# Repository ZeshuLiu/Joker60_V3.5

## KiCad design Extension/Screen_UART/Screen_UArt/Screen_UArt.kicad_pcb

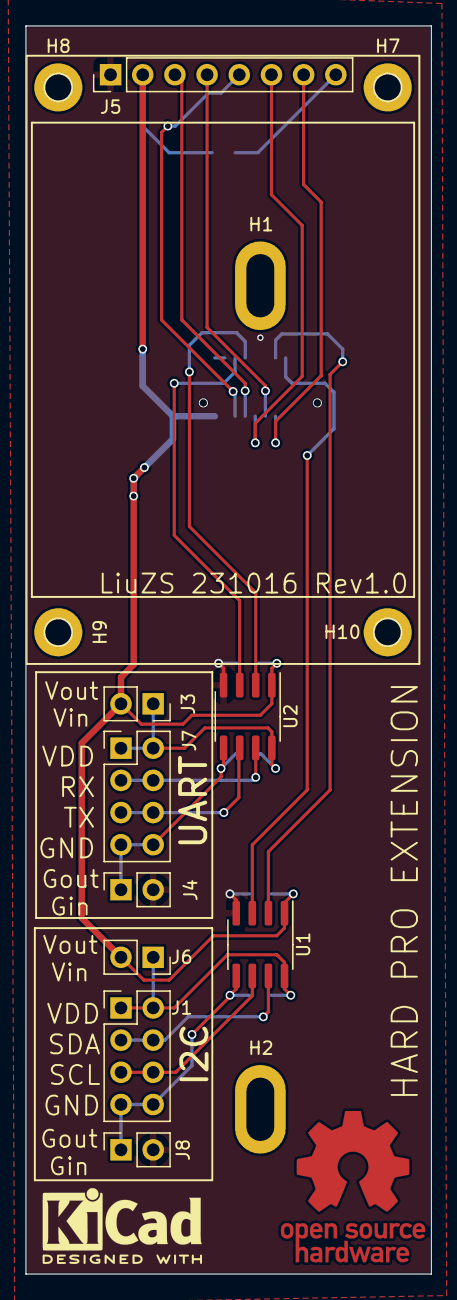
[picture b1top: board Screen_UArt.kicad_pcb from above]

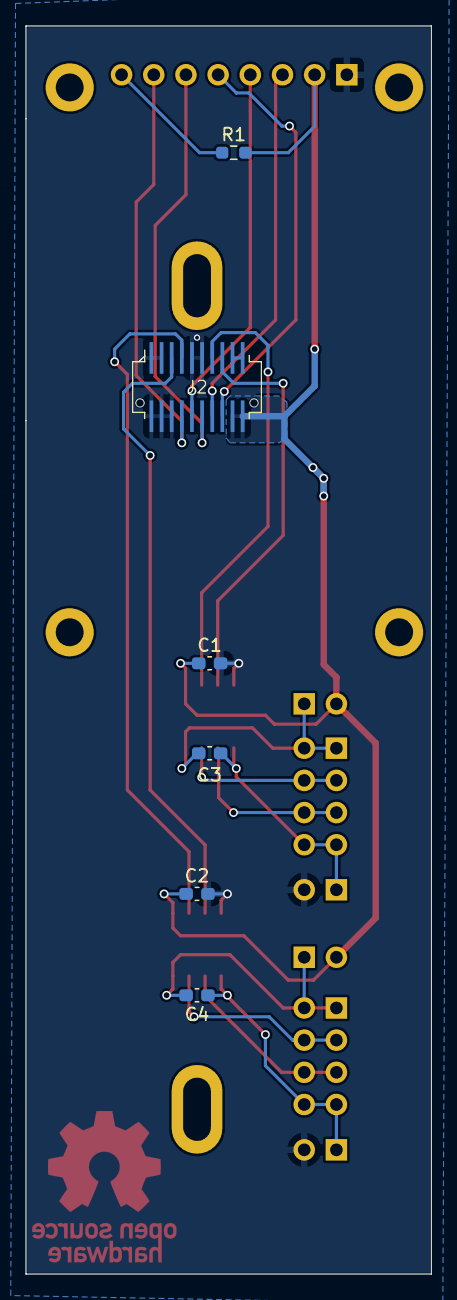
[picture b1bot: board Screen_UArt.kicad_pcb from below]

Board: 2 copper layers, 32.0 x 98.5 mm, 21 parts (6 on the bottom side), 21 nets.

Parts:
C1, C2, C3, C4: 100nf; C_0603_1608Metric_Pad1.08x0.95mm_HandSolder
H1, H2: MountingHole_Pad; MountingHole_M2_2.2x5mm_pad
H7, H8, H9, H10: MountingHole_Pad; MountingHole_2.2mm_M2_DIN965_Pad
J1, J7: Conn_02x04_Odd_Even; PinHeader_2x04_P2.54mm_Vertical
J2: Conn_02x10_Counter_Clockwise; BTB_0.8mm_2x10pin_Male
J3, J4, J6, J8: Conn_01x02_Pin; PinSocket_1x02_P2.54mm_Vertical
J5: Conn_01x08_Pin; PinHeader_1x08_P2.54mm_Vertical
R1: 10k; R_0603_1608Metric_Pad0.98x0.95mm_HandSolder
U1: ADuM1250; SOIC-8_3.9x4.9mm_P1.27mm
U2: ADuM1201BR; SOIC-8_3.9x4.9mm_P1.27mm

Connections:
+5V: J2.1, J2.2
/BLK: J5.8, R1.1
/MISO2: J2.16, J5.6
/MOSI2: J2.15, J5.4
/PB12: J2.18, J5.5
/PC8: J2.14, J5.7
/RXO: J7.3, J7.4, U2.7 (VIA)
/Rx6: J2.4, U2.2 (VOA)
/SCK2: J2.17, J5.3
/SCL3: J2.8, U1.3 (SCL1)
/SCLO: J1.5, J1.6, U1.6 (SCL2)
/SDA3: J2.7, U1.2 (SDA1)
/SDAO: J1.3, J1.4, U1.7 (SDA2)
/TXO: J7.5, J7.6, U2.6 (VOB)
/Tx6: J2.3, U2.3 (VIB)
GND: C1.2, C2.2, J2.5, J2.6, J2.9, J2.10, J2.11, J2.12, J2.13, J4.2, J5.1, J8.2, U1.4 (GND1), U2.4 (GND1)
GND1: C4.2, J1.7, J1.8, J8.1, U1.5 (GND2)
GNDA: C3.2, J4.1, J7.7, J7.8, U2.5 (GND2)
VDD: C1.1, C2.1, J2.19, J2.20, J3.2, J5.2, J6.2, R1.2, U1.1 (VDD1), U2.1 (VDD1)
VDDA: C3.1, J3.1, J7.1, J7.2, U2.8 (VDD2)
VDDF: C4.1, J1.1, J1.2, J6.1, U1.8 (VDD2)

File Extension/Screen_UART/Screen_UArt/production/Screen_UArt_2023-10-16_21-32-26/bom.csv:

Designator,Footprint,Quantity,Value,LCSC Part #
"C1, C2, C3, C4",0603,4,100nf,
"H1, H2",MountingHole_M2_2.2x5mm_pad,2,MountingHole_Pad,
"H10, H7, H8, H9",MountingHole_2.2mm_M2_DIN965_Pad,4,MountingHole_Pad,
"J1, J7",PinHeader_2x04_P2.54mm_Vertical,2,Conn_02x04_Odd_Even,
J2,BTB_0.8mm_2x10pin_Male,1,Conn_02x10_Counter_Clockwise,
"J3, J4, J6, J8",PinSocket_1x02_P2.54mm_Vertical,4,Conn_01x02_Pin,
J5,PinHeader_1x08_P2.54mm_Vertical,1,Conn_01x08_Pin,
R1,0603,1,10k,
U1,SOIC-8_3.9x4.9mm_P1.27mm,1,ADuM1250,
U2,SOIC-8_3.9x4.9mm_P1.27mm,1,ADuM1201BR,

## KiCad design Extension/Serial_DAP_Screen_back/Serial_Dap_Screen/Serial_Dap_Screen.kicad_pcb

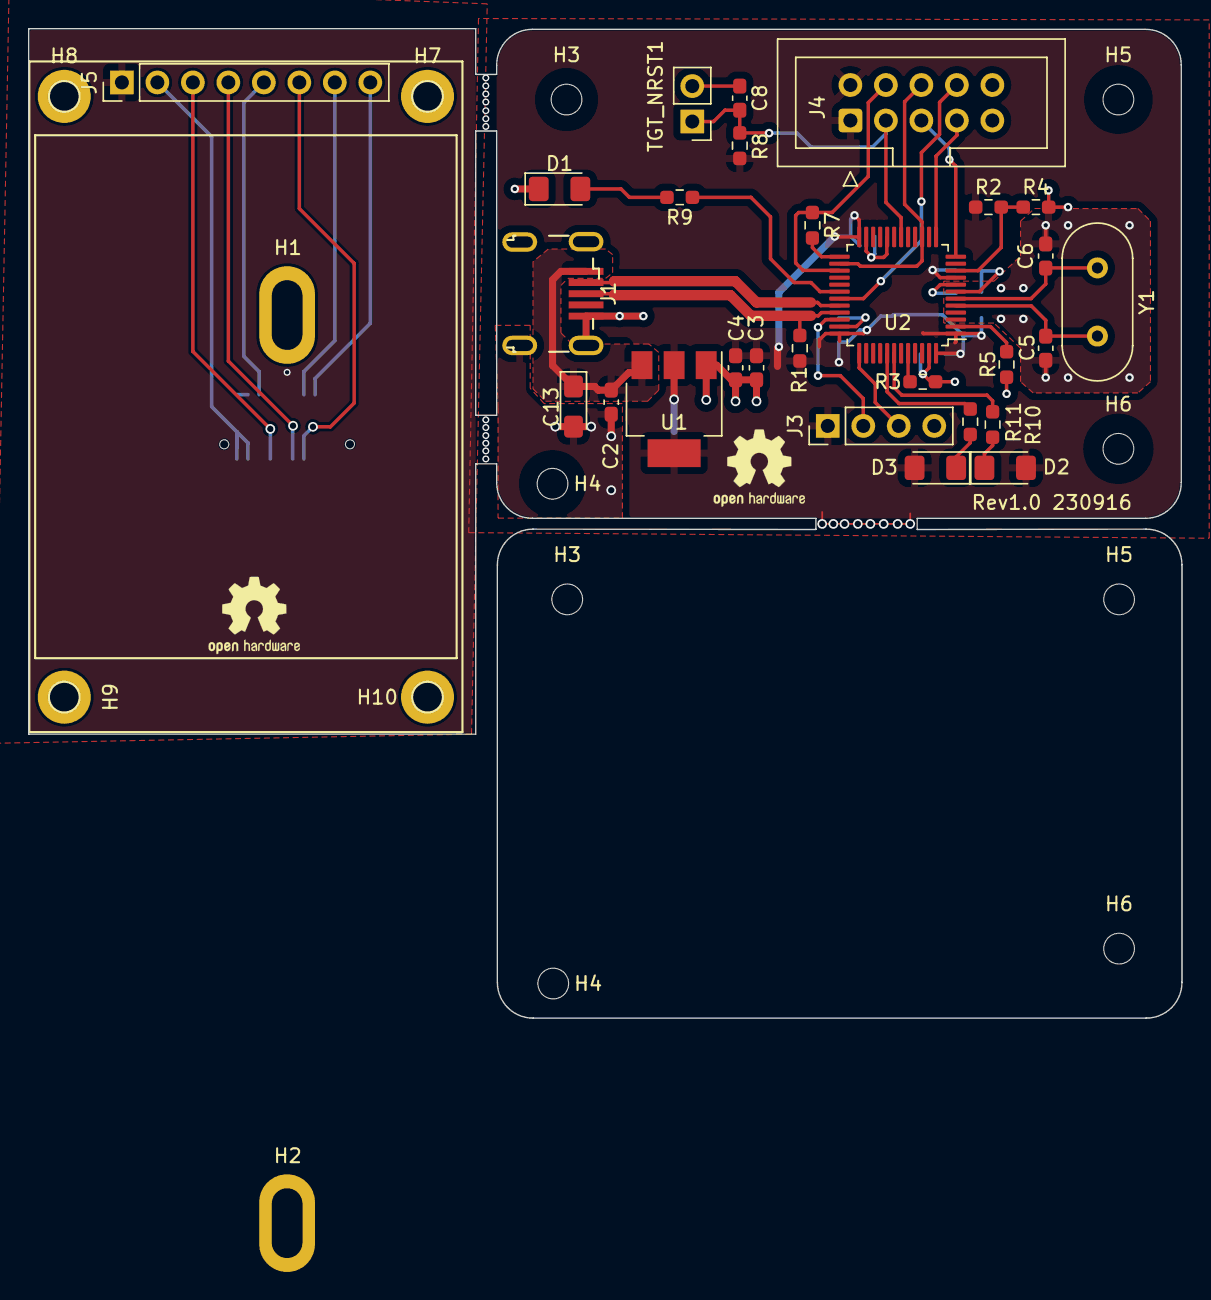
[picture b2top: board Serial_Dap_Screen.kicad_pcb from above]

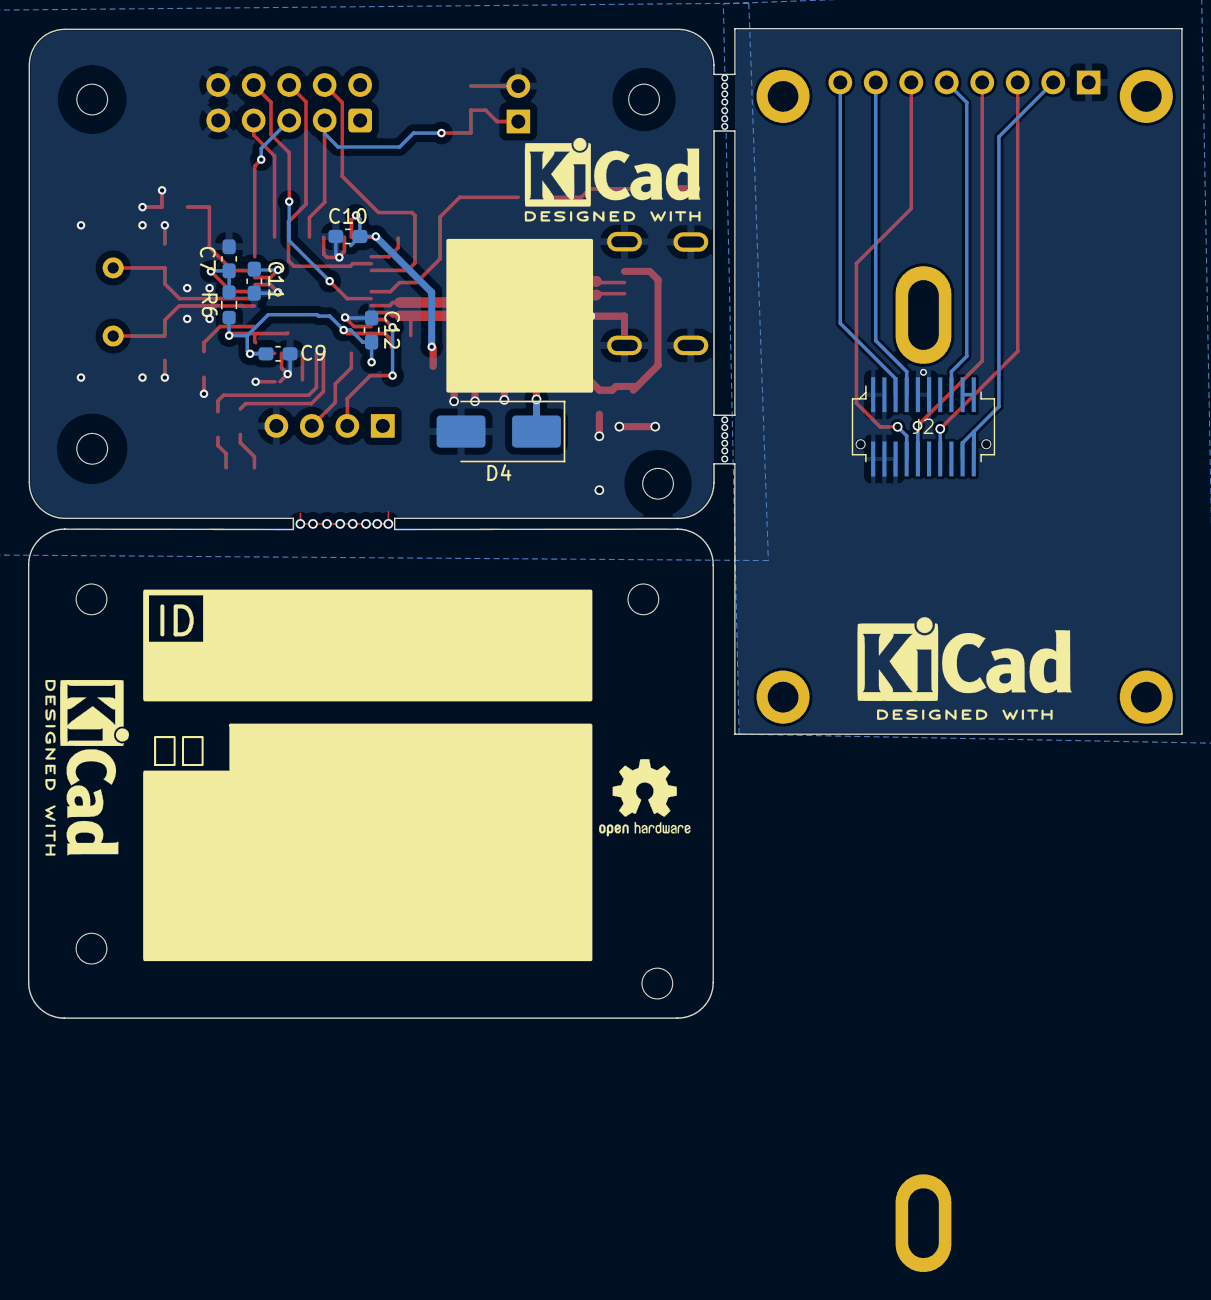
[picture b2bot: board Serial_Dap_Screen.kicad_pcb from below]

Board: 2 copper layers, 82.5 x 70.8 mm, 50 parts (8 on the bottom side), 32 nets.

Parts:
C2, C3, C7, C8, C9, C10, C11, C12: 100nf; C_0603_1608Metric_Pad1.08x0.95mm_HandSolder
C4: 10uf; C_0603_1608Metric_Pad1.08x0.95mm_HandSolder
C5, C6: 20pf; C_0603_1608Metric_Pad1.08x0.95mm_HandSolder
C13: 10uf; CP_EIA-3216-18_Kemet-A_Pad1.58x1.35mm_HandSolder
D1, D2, D3: LED; LED_1206_3216Metric_Pad1.42x1.75mm_HandSolder
D4: SMBJ3.3A; D_SMB_Handsoldering
H1, H2: MountingHole_Pad; MountingHole_M2_2.2x5mm_pad
H3, H3#2, H4, H4#2, H5, H5#2, H6, H6#2: MountingHole; MountingHole_2.2mm_M2
H7, H8, H9, H10: MountingHole_Pad; MountingHole_2.2mm_M2_DIN965_Pad
J1: USB_B_Mini; USB_Micro-B_4TH
J2: Conn_02x10_Counter_Clockwise; BTB_0.8mm_2x10pin_Male
J3: Conn_01x04_Pin; PinHeader_1x04_P2.54mm_Vertical
J4: Conn_02x05_Odd_Even; IDC-Header_2x05_P2.54mm_Vertical
J5: Conn_01x08_Pin; PinHeader_1x08_P2.54mm_Vertical
R1, R10: 1.5k; R_0603_1608Metric_Pad0.98x0.95mm_HandSolder
R2, R4: 4.7k; R_0603_1608Metric_Pad0.98x0.95mm_HandSolder
R3: 100k; R_0603_1608Metric_Pad0.98x0.95mm_HandSolder
R5, R6, R8: 10k; R_0603_1608Metric_Pad0.98x0.95mm_HandSolder
R7: 100; R_0603_1608Metric_Pad0.98x0.95mm_HandSolder
R9, R11: 470; R_0603_1608Metric_Pad0.98x0.95mm_HandSolder
TGT_NRST1: Conn_01x02_Pin; PinHeader_1x02_P2.54mm_Vertical
U1: AMS1117-3.3; SOT-223-3_TabPin2
U2: STM32F103CBTx; LQFP-48_7x7mm_P0.5mm
Y1: 8MHz; Crystal_HC49-U_Vertical

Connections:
+5V: C2.2, C13.1, J1.1 (VBUS), J2.1, J2.2, U1.3 (VI)
/IF_NRST: C7.2, R6.2, U2.7 (NRST)
/IF_SWCLK: J3.3, U2.37 (PA14)
/IF_SWDIO: J3.2, U2.34 (PA13)
/LED_COM_GREEN: R11.1, U2.41 (PB5)
/LED_DAP_BLUE: R10.1, U2.42 (PB6)
/LED_PWR_RED: R9.1, U2.30 (PA9)
/MOSI2: J2.15, J5.4
/PC8: J2.14, J5.6
/SCK2: J2.17, J5.3
/SCL3: J2.8, J5.8
/SDA3: J2.7, J5.7
/TGT_NRST: C8.2, J4.3, R8.2, TGT_NRST1.1, U2.18 (PB0)
/TGT_RX: J4.5, U2.12 (PA2)
/TGT_SWCLK: J4.6, U2.15 (PA5), U2.26 (PB13)
/TGT_SWDIO: J4.4, R7.1, U2.27 (PB14)
/TGT_SWO: J4.8, U2.31 (PA10)
/TGT_TX: J4.7, U2.13 (PA3)
/Tx6: J2.3, J5.5
/USB_D+: J1.3 (D+), R1.2, U2.33 (PA12)
/USB_D-: J1.2 (D-), U2.32 (PA11)
GND: C2.1, C3.1, C4.1, C5.1, C6.1, C7.1, C8.1, C9.1, C10.1, C11.1, C12.1, C13.2, D1.1 (K), D4.2 (A2), J1.5 (GND), J1.6 (Shield), J2.5, J2.6, J2.9, J2.10, J2.11, J2.12, J2.13, J3.4, J4.9, J4.10, J5.1, R3.1, R4.2, R5.2, TGT_NRST1.2, U1.1 (GND), U2.8 (VSSA), U2.20 (PB2), U2.23 (VSS), U2.35 (VSS), U2.47 (VSS)
unnamed: D1.2 (A), R9.2
unnamed: D2.1 (K), R10.2
unnamed: D3.1 (K), R11.2
unnamed: R3.2, U2.44 (BOOT0)
unnamed: R2.2, R4.1, U2.10 (PA0)
unnamed: R7.2, U2.25 (PB12)
unnamed: R5.1, U2.2 (PC13)
unnamed: C5.2, U2.5 (PD0), Y1.2
unnamed: C6.2, U2.6 (PD1), Y1.1
VDD: C3.2, C4.2, C9.2, C10.2, C11.2, C12.2, D2.2 (A), D3.2 (A), D4.1 (A1), J2.19, J2.20, J3.1, J4.1, J4.2, J5.2, R1.1, R2.1, R6.1, R8.1, U1.2 (VO), U2.1 (VBAT), U2.9 (VDDA), U2.24 (VDD), U2.36 (VDD), U2.48 (VDD)

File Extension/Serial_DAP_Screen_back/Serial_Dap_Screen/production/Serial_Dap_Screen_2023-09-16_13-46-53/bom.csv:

Designator,Footprint,Quantity,Value,LCSC Part #
"C10, C11, C12, C2, C3, C7, C8, C9",0603,8,100nf,
C13,CP_EIA-3216-18_Kemet-A_Pad1.58x1.35mm_HandSolder,1,10uf,
C4,0603,1,10uf,
"C5, C6",0603,2,20pf,
"D1, D2, D3",1206,3,LED,
D4,D_SMB_Handsoldering,1,SMBJ3.3A,
"H1, H2",MountingHole_M2_2.2x5mm_pad,2,MountingHole_Pad,
"H10, H7, H8, H9",MountingHole_2.2mm_M2_DIN965_Pad,4,MountingHole_Pad,
"H3_2, H3, H4_2, H4, H5_2, H5, H6_2, H6",MountingHole_2.2mm_M2,8,MountingHole,
J1,USB_Micro-B_4TH,1,USB_B_Mini,
J2,BTB_0.8mm_2x10pin_Male,1,Conn_02x10_Counter_Clockwise,
J3,PinHeader_1x04_P2.54mm_Vertical,1,Conn_01x04_Pin,
J4,IDC-Header_2x05_P2.54mm_Vertical,1,Conn_02x05_Odd_Even,
J5,PinHeader_1x08_P2.54mm_Vertical,1,Conn_01x08_Pin,
"R1, R10",0603,2,1.5k,
"R11, R9",0603,2,470,
"R2, R4",0603,2,4.7k,
R3,0603,1,100k,
"R5, R6, R8",0603,3,10k,
R7,0603,1,100,
TGT_NRST1,PinHeader_1x02_P2.54mm_Vertical,1,Conn_01x02_Pin,
U1,SOT-223-3_TabPin2,1,AMS1117-3.3,
U2,LQFP-48_7x7mm_P0.5mm,1,STM32F103CBTx,
Y1,Crystal_HC49-U_Vertical,1,8MHz,

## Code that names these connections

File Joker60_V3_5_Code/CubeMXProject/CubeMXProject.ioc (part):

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Mcu.Name=STM32F401R(B-C)Tx
Mcu.Package=LQFP64
Mcu.UserName=STM32F401RCTx
PA0-WKUP.GPIOParameters=GPIO_Speed,PinState,GPIO_Label
PA0-WKUP.GPIO_Label=ROW5
PA0-WKUP.GPIO_Speed=GPIO_SPEED_FREQ_VERY_HIGH
PA0-WKUP.PinState=GPIO_PIN_SET
PA0-WKUP.Signal=GPIO_Output
PA1.GPIOParameters=GPIO_PuPd,GPIO_Label
PA1.GPIO_Label=COL5
PA1.GPIO_PuPd=GPIO_PULLUP
PA1.Signal=GPIO_Input
PA11.GPIOParameters=GPIO_Label
PA11.GPIO_Label=USB_N
PA11.Mode=Device_Only
PA11.Signal=USB_OTG_FS_DM
PA12.GPIOParameters=GPIO_Label
PA12.GPIO_Label=USB_P
PA12.Mode=Device_Only
PA12.Signal=USB_OTG_FS_DP
PA13.GPIOParameters=GPIO_Label
PA13.GPIO_Label=SWDIO
PA13.Mode=Serial_Wire
PA13.Signal=SYS_JTMS-SWDIO
PA14.GPIOParameters=GPIO_Label
PA14.GPIO_Label=SWDCLK
PA14.Mode=Serial_Wire
PA14.Signal=SYS_JTCK-SWCLK
PA15.GPIOParameters=GPIO_Speed,PinState,GPIO_PuPd,GPIO_Label,GPIO_ModeDefaultOutputPP
PA15.GPIO_Label=ROW1
PA15.GPIO_ModeDefaultOutputPP=GPIO_MODE_OUTPUT_PP
PA15.GPIO_PuPd=GPIO_NOPULL
PA15.GPIO_Speed=GPIO_SPEED_FREQ_VERY_HIGH
PA15.PinState=GPIO_PIN_SET
PA15.Signal=GPIO_Output
PA2.GPIOParameters=GPIO_PuPd,GPIO_Label
PA2.GPIO_Label=COL4
PA2.GPIO_PuPd=GPIO_PULLUP
PA2.Signal=GPIO_Input
PA3.GPIOParameters=GPIO_PuPd,GPIO_Label
PA3.GPIO_Label=COL1
PA3.GPIO_PuPd=GPIO_PULLUP
PA3.Signal=GPIO_Input
PA4.GPIOParameters=GPIO_PuPd,GPIO_Label
PA4.GPIO_Label=COL2
PA4.GPIO_PuPd=GPIO_PULLUP
PA4.Signal=GPIO_Input
PA5.GPIOParameters=GPIO_PuPd,GPIO_Label
PA5.GPIO_Label=COL3
PA5.GPIO_PuPd=GPIO_PULLUP
PA5.Signal=GPIO_Input
PA6.GPIOParameters=GPIO_Speed,PinState,GPIO_PuPd,GPIO_Label,GPIO_ModeDefaultOutputPP
PA6.GPIO_Label=LED1
PA6.GPIO_ModeDefaultOutputPP=GPIO_MODE_OUTPUT_OD
PA6.GPIO_PuPd=GPIO_PULLUP
PA6.GPIO_Speed=GPIO_SPEED_FREQ_LOW
PA6.PinState=GPIO_PIN_SET
PA6.Signal=GPIO_Output
PA7.GPIOParameters=GPIO_Speed,PinState,GPIO_PuPd,GPIO_Label,GPIO_ModeDefaultOutputPP
PA7.GPIO_Label=LED2
PA7.GPIO_ModeDefaultOutputPP=GPIO_MODE_OUTPUT_OD
PA7.GPIO_PuPd=GPIO_PULLUP
PA7.GPIO_Speed=GPIO_SPEED_FREQ_LOW
PA7.PinState=GPIO_PIN_SET
PA7.Signal=GPIO_Output
PA8.GPIOParameters=GPIO_Label
PA8.GPIO_Label=SCL3
PA8.Mode=I2C
PA8.Signal=I2C3_SCL
PB13.GPIOParameters=GPIO_Label
PB13.GPIO_Label=SCK2
PB13.Mode=Full_Duplex_Master
PB13.Signal=SPI2_SCK
PB14.GPIOParameters=GPIO_Label
PB14.GPIO_Label=MISO2
PB14.Mode=Full_Duplex_Master
PB14.Signal=SPI2_MISO
PB15.GPIOParameters=GPIO_Label
PB15.GPIO_Label=MOSI2
PB15.Mode=Full_Duplex_Master
PB15.Signal=SPI2_MOSI
PB3.GPIOParameters=GPIO_PuPd,GPIO_Label
PB3.GPIO_Label=COL13
PB3.GPIO_PuPd=GPIO_PULLUP
PB3.Signal=GPIO_Input
PB4.GPIOParameters=GPIO_PuPd,GPIO_Label
PB4.GPIO_Label=COL14
PB4.GPIO_PuPd=GPIO_PULLUP
PB4.Signal=GPIO_Input
PB5.GPIOParameters=GPIO_Speed,PinState,GPIO_PuPd,GPIO_Label
PB5.GPIO_Label=ROW3
PB5.GPIO_PuPd=GPIO_NOPULL
PB5.GPIO_Speed=GPIO_SPEED_FREQ_VERY_HIGH
PB5.PinState=GPIO_PIN_SET
PB5.Signal=GPIO_Output
PB6.GPIOParameters=GPIO_PuPd,GPIO_Label
PB6.GPIO_Label=COL6
PB6.GPIO_PuPd=GPIO_PULLUP
PB6.Signal=GPIO_Input
PB7.GPIOParameters=GPIO_PuPd,GPIO_Label
PB7.GPIO_Label=COL7
PB7.GPIO_PuPd=GPIO_PULLUP
PB7.Signal=GPIO_Input
PB8.GPIOParameters=GPIO_PuPd,GPIO_Label
PB8.GPIO_Label=COL8
PB8.GPIO_PuPd=GPIO_PULLUP
PB8.Signal=GPIO_Input
PB9.GPIOParameters=GPIO_PuPd,GPIO_Label
PB9.GPIO_Label=COL9
PB9.GPIO_PuPd=GPIO_PULLUP
PB9.Signal=GPIO_Input
PC10.GPIOParameters=GPIO_Speed,PinState,GPIO_PuPd,GPIO_Label,GPIO_ModeDefaultOutputPP
PC10.GPIO_Label=ROW2
PC10.GPIO_ModeDefaultOutputPP=GPIO_MODE_OUTPUT_PP
PC10.GPIO_PuPd=GPIO_PULLUP
PC10.GPIO_Speed=GPIO_SPEED_FREQ_VERY_HIGH
PC10.PinState=GPIO_PIN_SET
PC10.Signal=GPIO_Output
PC11.GPIOParameters=GPIO_PuPd,GPIO_Label
PC11.GPIO_Label=COL10
PC11.GPIO_PuPd=GPIO_PULLUP
PC11.Signal=GPIO_Input
PC12.GPIOParameters=GPIO_PuPd,GPIO_Label
PC12.GPIO_Label=COL11
PC12.GPIO_PuPd=GPIO_PULLUP
PC12.Signal=GPIO_Input
PC13-ANTI_TAMP.GPIOParameters=GPIO_Speed,PinState,GPIO_PuPd,GPIO_Label,GPIO_ModeDefaultOutputPP
PC13-ANTI_TAMP.GPIO_Label=ROW4
PC13-ANTI_TAMP.GPIO_ModeDefaultOutputPP=GPIO_MODE_OUTPUT_PP
PC13-ANTI_TAMP.GPIO_PuPd=GPIO_PULLUP
PC13-ANTI_TAMP.GPIO_Speed=GPIO_SPEED_FREQ_LOW
PC13-ANTI_TAMP.PinState=GPIO_PIN_SET
PC13-ANTI_TAMP.Signal=GPIO_Output
PC6.GPIOParameters=GPIO_Label
PC6.GPIO_Label=TX6
PC6.Mode=Asynchronous
PC6.Signal=USART6_TX
PC7.GPIOParameters=GPIO_Label
PC7.GPIO_Label=RX6
PC7.Mode=Asynchronous
PC7.Signal=USART6_RX
PC9.GPIOParameters=GPIO_Label
PC9.GPIO_Label=SDA3
PC9.Mode=I2C
PC9.Signal=I2C3_SDA
PD2.GPIOParameters=GPIO_PuPd,GPIO_Label
PD2.GPIO_Label=COL12
PD2.GPIO_PuPd=GPIO_PULLUP
PD2.Signal=GPIO_Input
PH0\ -\ OSC_IN.Mode=HSE-External-Oscillator
PH0\ -\ OSC_IN.Signal=RCC_OSC_IN
PH1\ -\ OSC_OUT.Mode=HSE-External-Oscillator
PH1\ -\ OSC_OUT.Signal=RCC_OSC_OUT
RCC.HSE_VALUE=25000000
RCC.SYSCLKFreq_VALUE=84000000
RCC.SYSCLKSource=RCC_SYSCLKSOURCE_PLLCLK
board=custom

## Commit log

2023-08-13 Start Building
    Using Stm32f401, f103 should be compatible
2023-08-14 230814SchoolPC
2023-08-15 230815_SchoolPC
    PCB layout
    CubeMX Pin configuration
2023-08-16 230816_SchoolPC
2023-08-19 230817_schoolPC
2023-08-19 Bom revised
2023-08-19 del some files
2023-08-19 clean
2023-08-26 Update build
2023-08-26 加入注释
2023-08-26 键盘正常使用&加入了fn层的HOME等按键
2023-09-02 Composite worked
2023-09-02 del build
2023-09-02 build file
2023-09-02 modified: Joker60_V3_5_Code/Composite/Core/Src/freertos.c
2023-10-16 U-Art (HARD PRO EXT)
2023-10-16 cache
2023-10-21 Uart Ext code
2023-10-22 FN键按下后不会取消两层相同的按键的发送，整理了HIDreport的数组
2023-10-23 BACKUPS
2023-10-23 logs
2023-10-28 case for screen start
2023-10-29 新屏幕的盖子
2023-11-04 Update Composite.code-workspace
2023-11-04 U ART 驱动部分完成
    现在可以作为USB 转串口工作
    屏幕上显示波特率信息
    屏幕上预留显示发送接收计数以及十六进制显示的位置
2023-11-12 cmd disp
2023-11-14 可以正常工作，键盘配置了函数数组，可以实现功能。目前可以PN + L 锁定键盘
2023-11-14 Revert "Merge branch 'main' of https://github.com/LiuZSChina/Joker60_V3.5"
    This reverts commit f7dbcc8b97f77df3b8c12e592d12a385700dcbc6, reversing
    changes made to 83d9d34583c502e71123a5b2a04d3d8099b75dd8.
2023-11-28 new part
2023-12-08 串口调试助手二进制显示功能
2024-01-23 更改滤波次数为10次，优化等级为O3
2024-07-02 更改了滤波逻辑，滤波效果应该会更好
    主要是增加了松开按键的延时阶段，这样的话可以更好的滤波防止连击的情况出现
2025-12-26 移植到了CubeIDE工程，还未测试
2025-12-26 重新整理，并未测试
2025-12-26 更新gitignore
2025-12-26 CUBEIDE测试OK；串口buffer改大（10kByte/s）测试完成
2025-12-29 清理USB CDC接收中的代码其余功能移至主循环进行【已测试】
2026-01-21 优化屏幕盖子
